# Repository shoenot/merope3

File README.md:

# Merope
## 68 key split mechanical keyboard

Merope is a split mechanical keyboard design based vaguely off the lily58 and other common split keyboards. This one has what I consider to be a pretty agressive colstag. 
There are 7 main columns of 4 rows (for basically 60% coverage), plus 2 mod row keys, 3 thumb cluster keys, and an inner key above the thumb cluster. Key layout and pictures TBA after I get my hands on everything (PCB currently being fabbed)

Don't have an ergogen as I did the whole thing in KiCad, but here's how the plate looks:

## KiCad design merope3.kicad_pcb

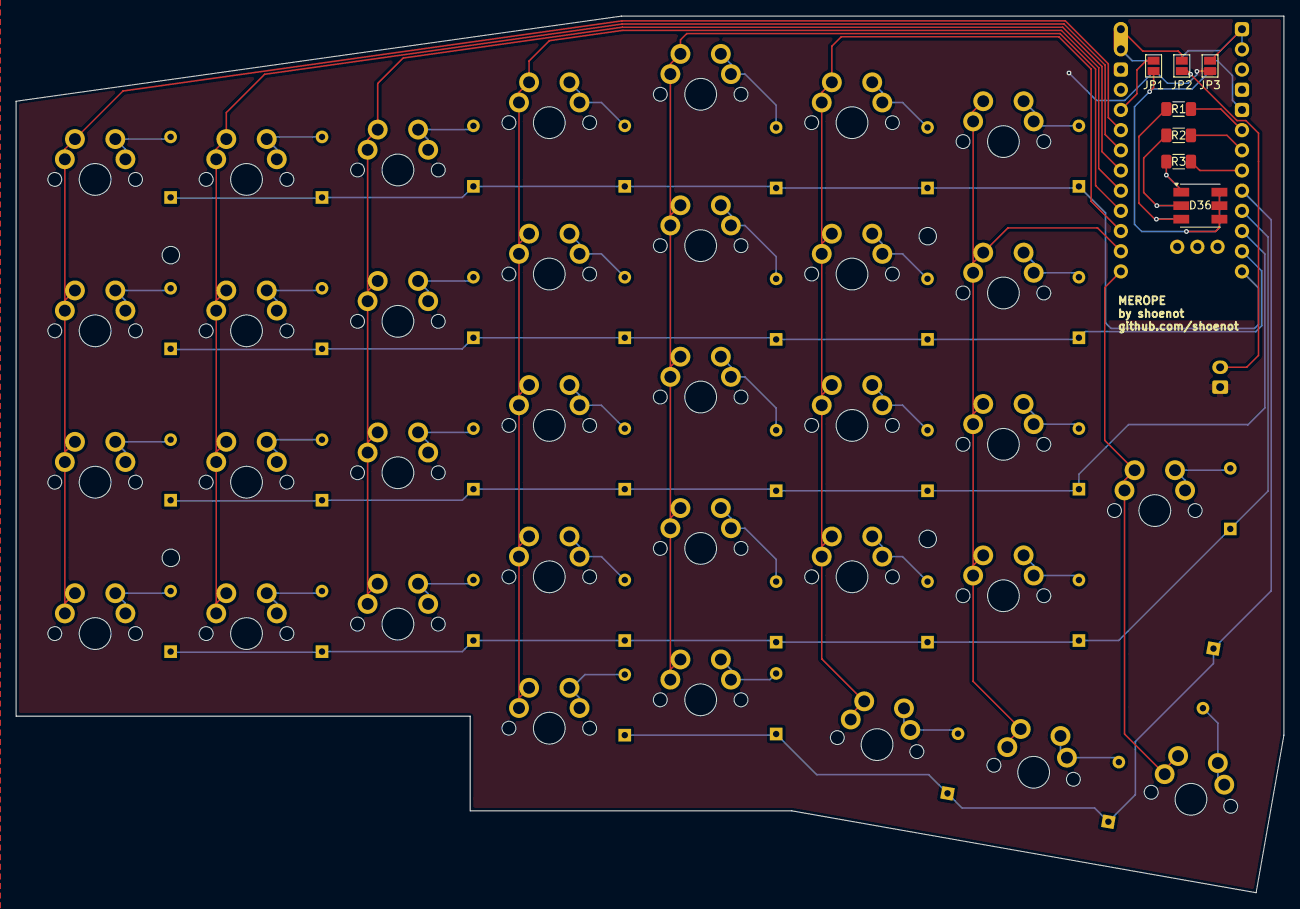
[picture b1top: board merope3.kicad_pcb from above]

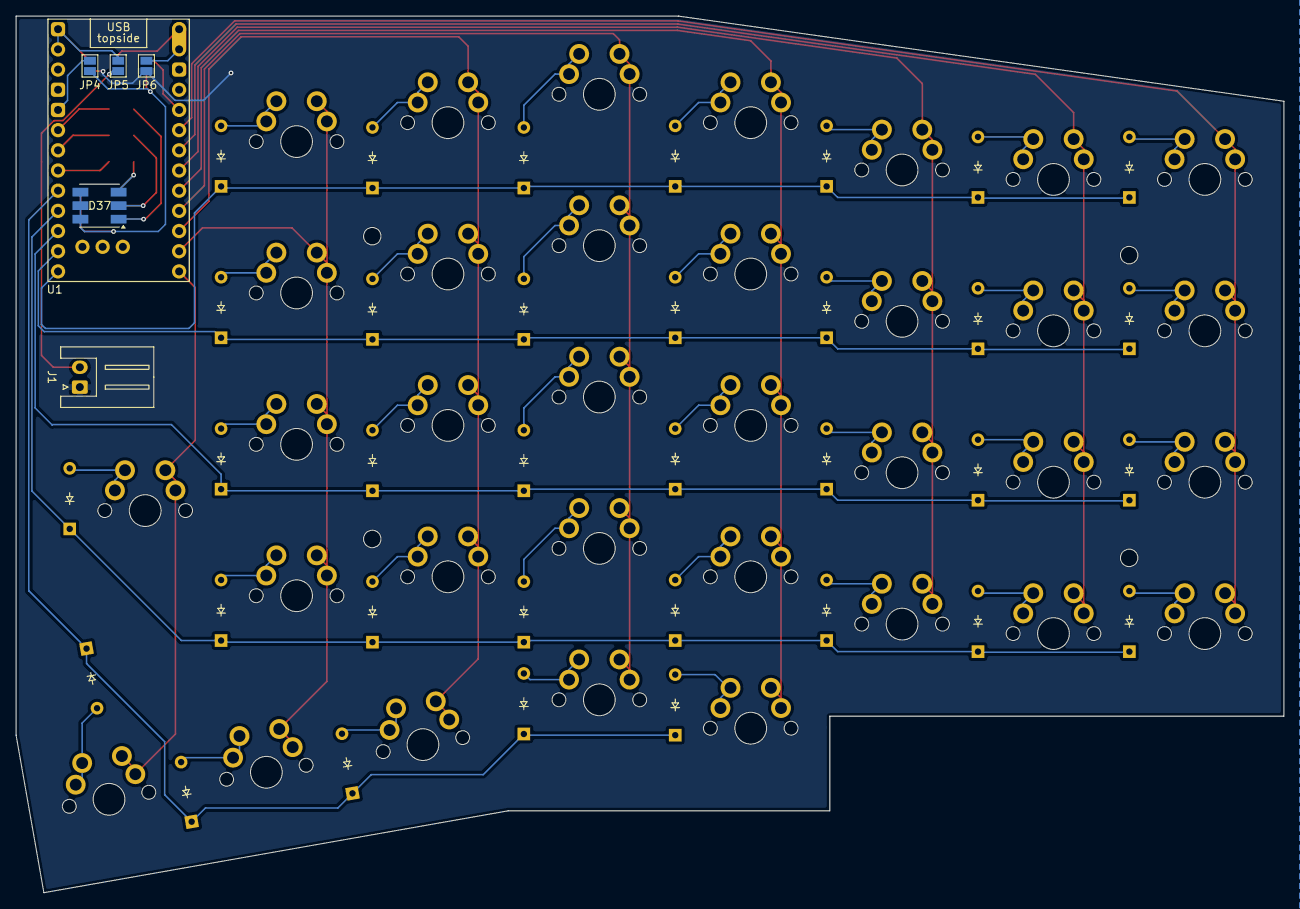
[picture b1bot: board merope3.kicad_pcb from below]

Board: 2 copper layers, 159.5 x 110.3 mm, 81 parts (40 on the bottom side), 60 nets.

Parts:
D1, D2, D3, D4, D5, D6, D7, D8, D9, D10, D11, D12, D13, D14, D15, D16, D17, D18, D19, D20, D21, D22, D23, D24, D25, D26, D27, D28, D29, D31, D32, D33, D34, D35: D; Diode_DO-35
D36, D37: LED_RGB; LED_RGB_5050-6
J1: Conn_01x02_Socket; JST_XH_S2B-XH-A_1x02_P2.50mm_Horizontal
JP1: 3V3 SIDE A; SolderJumper-2_P1.3mm_Open_Pad1.0x1.5mm
JP2: PWR SIDE A; SolderJumper-2_P1.3mm_Open_Pad1.0x1.5mm
JP3: GND SIDE A; SolderJumper-2_P1.3mm_Open_Pad1.0x1.5mm
JP4: 3V3 SIDE B; SolderJumper-2_P1.3mm_Open_Pad1.0x1.5mm
JP5: PWR SIDE B; SolderJumper-2_P1.3mm_Open_Pad1.0x1.5mm
JP6: GND SIDE B; SolderJumper-2_P1.3mm_Open_Pad1.0x1.5mm
R1, R2, R3: R_Small_US; R_1206_3216Metric_Pad1.30x1.75mm_HandSolder
SW1, SW2, SW3, SW4, SW5, SW6, SW7, SW8, SW9, SW10, SW11, SW12, SW13, SW14, SW15, SW16, SW17, SW18, SW19, SW20, SW21, SW22, SW23, SW24, SW25, SW26, SW27, SW28, SW29, SW30, SW31, SW32, SW33, SW34: SW_Push; MX_Solder_1.00u_Reversible
U1: SuperMini nRF52840; SuperMini_nRF52840_AH_USBup

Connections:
/3V3: D36.4 (BA), D36.5 (GA), D36.6 (RA), D37.4 (BA), D37.5 (GA), D37.6 (RA), JP1.2 (B), JP4.2 (B)
/3V3 MAIN: JP1.1 (A), U1.16 (3V3)
/3v3 REV: JP4.1 (A), U1.4 (GND)
/BAT MAIN: JP2.1 (A), JP6.1 (A), U1.13 (BAT+), U1.29 (BAT+)
/BAT REV: JP3.1 (A), JP5.1 (A), U1.1 (P0.06), U1.28 (GND)
/GND: J1.1, JP3.2 (B), JP6.2 (B)
/LED1: R3.2, U1.7 (P0.22)
/LED2: R2.2, U1.6 (P0.20)
/LED3: R1.2, U1.5 (P0.17)
/LED_R1: D36.1 (RK), D37.3 (BK), R3.1
/LED_R2: D36.2 (GK), D37.2 (GK), R2.1
/LED_R3: D36.3 (BK), D37.1 (RK), R1.1
/PWR: J1.2, JP2.2 (B), JP5.2 (B)
COL0: SW1.1, SW8.1, SW15.1, SW22.1, U1.17 (P0.31-LF)
COL1: SW2.1, SW9.1, SW16.1, SW23.1, U1.18 (P0.29-LF)
COL2: SW3.1, SW10.1, SW17.1, SW24.1, U1.19 (P0.02-LF)
COL3: SW4.1, SW11.1, SW18.1, SW25.1, SW30.1, U1.20 (P1.15-LF)
COL4: SW5.1, SW12.1, SW19.1, SW26.1, SW31.1, U1.21 (P1.13-LF)
COL5: SW6.1, SW13.1, SW20.1, SW27.1, SW32.1, U1.22 (P1.11-LF)
COL6: SW7.1, SW14.1, SW21.1, SW28.1, SW33.1, U1.23 (P0.10-LF)
COL7: SW29.1, SW34.1, U1.24 (P0.09-LF)
unnamed: D1.2 (A), SW1.2
unnamed: D2.2 (A), SW2.2
unnamed: D3.2 (A), SW3.2
unnamed: D4.2 (A), SW4.2
unnamed: D5.2 (A), SW5.2
unnamed: D6.2 (A), SW6.2
unnamed: D7.2 (A), SW7.2
unnamed: D8.2 (A), SW8.2
unnamed: D9.2 (A), SW9.2
unnamed: D10.2 (A), SW10.2
unnamed: D11.2 (A), SW11.2
unnamed: D12.2 (A), SW12.2
unnamed: D13.2 (A), SW13.2
unnamed: D14.2 (A), SW14.2
unnamed: D15.2 (A), SW15.2
unnamed: D16.2 (A), SW16.2
unnamed: D17.2 (A), SW17.2
unnamed: D18.2 (A), SW18.2
unnamed: D19.2 (A), SW19.2
unnamed: D20.2 (A), SW20.2
unnamed: D21.2 (A), SW21.2
unnamed: D22.2 (A), SW22.2
unnamed: D23.2 (A), SW23.2
unnamed: D24.2 (A), SW24.2
unnamed: D25.2 (A), SW25.2
unnamed: D26.2 (A), SW26.2
unnamed: D27.2 (A), SW27.2
unnamed: D28.2 (A), SW28.2
unnamed: D29.2 (A), SW29.2
unnamed: D31.2 (A), SW30.2
unnamed: D32.2 (A), SW31.2
unnamed: D33.2 (A), SW32.2
unnamed: D34.2 (A), SW33.2
unnamed: D35.2 (A), SW34.2
ROW0: D1.1 (K), D2.1 (K), D3.1 (K), D4.1 (K), D5.1 (K), D6.1 (K), D7.1 (K), U1.12 (P1.06-LF)
ROW1: D8.1 (K), D9.1 (K), D10.1 (K), D11.1 (K), D12.1 (K), D13.1 (K), D14.1 (K), U1.11 (P1.04-LF)
ROW2: D15.1 (K), D16.1 (K), D17.1 (K), D18.1 (K), D19.1 (K), D20.1 (K), D21.1 (K), U1.10 (P0.11)
ROW3: D22.1 (K), D23.1 (K), D24.1 (K), D25.1 (K), D26.1 (K), D27.1 (K), D28.1 (K), D29.1 (K), U1.9 (P1.00)
ROW4: D31.1 (K), D32.1 (K), D33.1 (K), D34.1 (K), D35.1 (K), U1.8 (P0.24)

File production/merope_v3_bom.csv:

Designator,Footprint,Quantity,Value,LCSC Part #
"D1, D10, D11, D12, D13, D14, D15, D16, D17, D18, D19, D2, D20, D21, D22, D23, D24, D25, D26, D27, D28, D29, D3, D31, D32, D33, D34, D35, D4, D5, D6, D7, D8, D9",Diode_DO-35,34,D,
"D36, D37",LED_RGB_5050-6,2,LED_RGB,
J1,JST_XH_S2B-XH-A_1x02_P2.50mm_Horizontal,1,Conn_01x02_Socket,
"R1, R2, R3",1206,3,R_Small_US,
"SW1, SW10, SW11, SW12, SW13, SW14, SW15, SW16, SW17, SW18, SW19, SW2, SW20, SW21, SW22, SW23, SW24, SW25, SW26, SW27, SW28, SW29, SW3, SW30, SW31, SW32, SW33, SW34, SW4, SW5, SW6, SW7, SW8, SW9",MX_Solder_1.00u_Reversible,34,SW_Push,
